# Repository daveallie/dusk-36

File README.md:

<h1 align="center">Dusk 36 Keyboard</h1>

Dusk 36 is a 36-key low-profile split ergo keyboard based off https://github.com/weteor/3W6 and 
https://github.com/davidphilipbarr/Sweep.

The Dusk 36 is designed around the nice!nano v2.0 microcontroller in order to be a true wireless keyboard (no cables
between halves or from the keyboard to the computer). This board's layout was generated with 
[my fork of Ergogen](https://github.com/daveallie/ergogen/tree/daveallie-improvements) (which includes a few small 
changes), and then routed by hand in KiCad.

### PCB Preview

| Left                   | Right                   |
|------------------------|-------------------------|
|  |  |

### BOM

**Hardware for PCB**
- 2 x [nice!nano v2.0](https://keebd.com/products/nice-nano?variant=41688983240856)
- 1 x [Kailh Low Profile Switches Hot-swappable PCB Socket Sip socket Hot Plug (50 pack)](https://www.aliexpress.com/item/1005003575767699.html)
- 2 x [40 Pin Machined IC Breakable Female Header Strip](https://keebd.com/products/40-pin-machined-ic-breakable-female-header-strip?variant=40383060410520)
- Pins (pick one)
  - 48 x [Single Post Terminal Connector Through Hole Gold 0.020" (0.51mm) Dia](https://www.digikey.com.au/en/products/detail/mill-max-manufacturing-corp/3320-0-00-15-00-00-03-0/4147392)
  - 2 x [Mill-Max Low Profile Controller Pins (Pack of 25)](https://keebd.com/products/mill-max-low-profile-controller-pins-pack-of-25?variant=41055232458904)
- 2 x [EG1215AA Switch](https://www.digikey.com.au/en/products/detail/e-switch/EG1215AA/9559277)
- 2 x [PTS636 SK43 LFS button](https://www.digikey.com.au/en/products/detail/c-k/PTS636-SK43-LFS/10071716)
- 2 x [Polymer Lithium Ion Battery (LiPo) 3.7V 120mAh](https://core-electronics.com.au/lipo-polymer-lithium-ion-battery-120mah.html)
- 36 x SOD-123 diode

**Switches and Keycaps**
- 4 x [Kailh low profile Switch 1350 Chocolate Keyboard Switch RGB SMD kailh Mechanical Keyboard white stem clicky hand feeling (10 pack)](https://www.aliexpress.com/item/32959996455.html)
- 3 x [MBK Low Profile Keycaps - 1u Black (10 pack)](https://keebd.com/products/mbk-low-profile-keycaps?variant=41506944909464)
- 1 x [MBK Low Profile Keycaps - 1u Homing White (2 pack)](https://keebd.com/products/mbk-low-profile-keycaps?variant=41506944811160)
- 1 x [MBK Low Profile Keycaps - 1.5u Black (5 pack)](https://keebd.com/products/mbk-low-profile-keycaps?variant=41506944975000)

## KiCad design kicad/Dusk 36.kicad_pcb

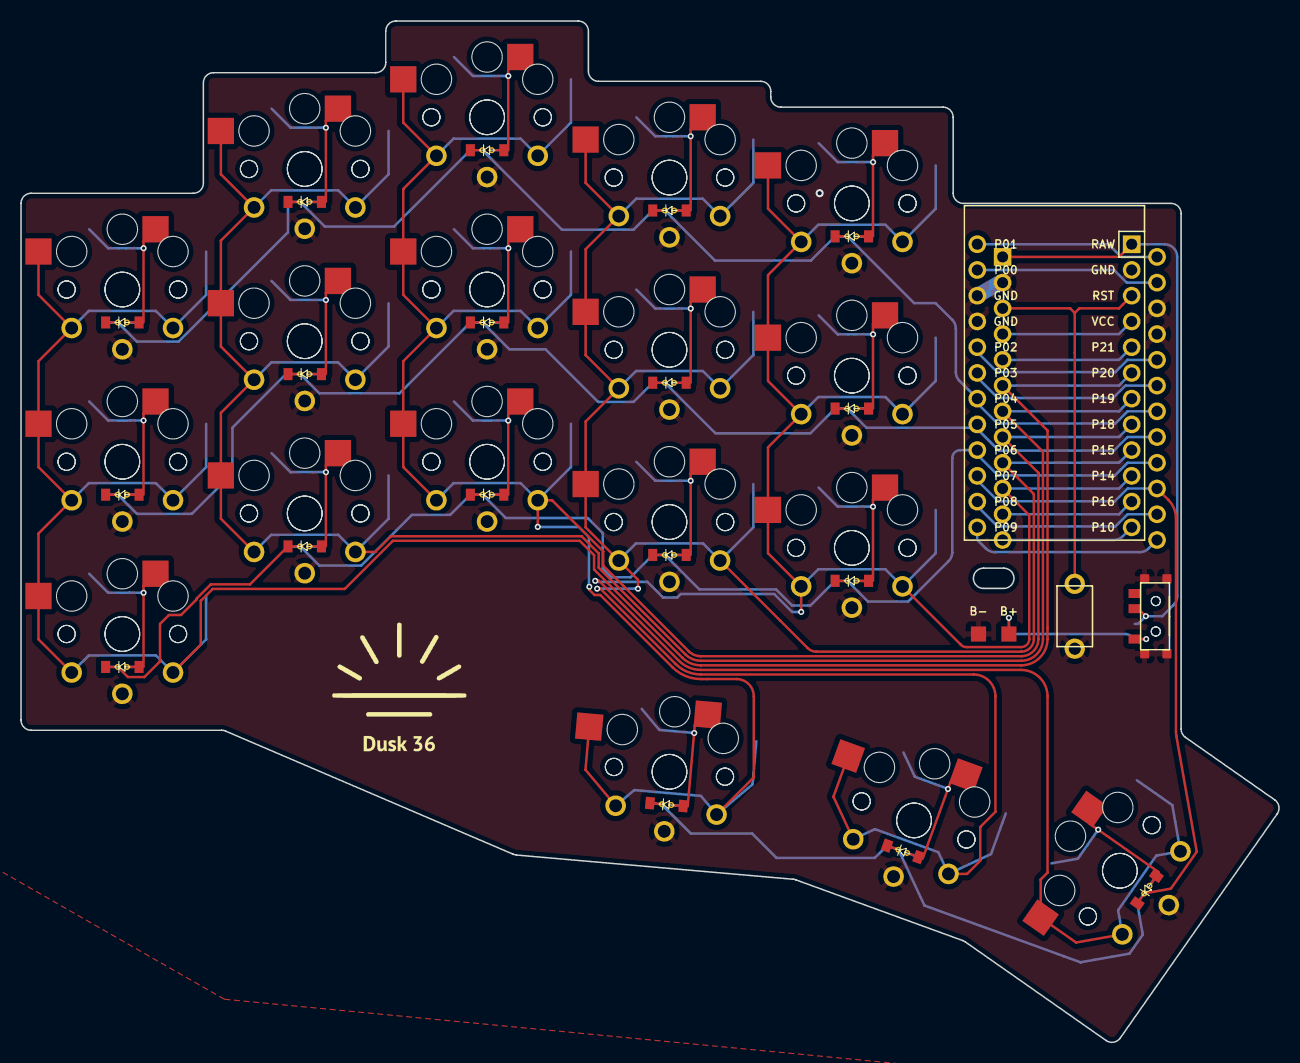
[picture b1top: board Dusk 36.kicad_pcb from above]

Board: 2 copper layers, 124.2 x 100.8 mm, 61 parts (1 on the bottom side), 41 nets.

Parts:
B1: SW_TACT_PTS636_SK43_LFS
D1, D2, D3, D4, D5, D6, D7, D8, D9, D10, D11, D12, D13, D14, D15, D16, D17, D18: ComboDiode
MCU1, MCU2: ProMicro
PAD1, PAD2: SMDPad
S1, S2, S3, S4, S5, S6, S7, S8, S9, S10, S11, S12, S13, S14, S15, S16, S17, S18, S19, S20, S21, S22, S23, S24, S25, S26, S27, S28, S29, S30, S31, S32, S33, S34, S35, S36: PG1350
T1, T2: SPDT_C128955

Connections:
BPos: PAD1.1, T1.1, T2.3
GND: B1.1, MCU1.2, MCU1.15, MCU1.16, MCU2.2, MCU2.15, MCU2.16, PAD2.1, S2.2, S4.2, S6.2, S8.2, S10.2, S12.2, S14.2, S16.2, S18.2, S20.2, S22.2, S24.2, S26.2, S28.2, S30.2, S32.2, S34.2, S36.2
P0: MCU1.14, MCU2.14
P1: MCU1.13, MCU2.13
P2: MCU1.17, MCU2.17
P3: MCU1.18, MCU2.18
P4: D3.1, D6.1, D9.1, D12.1, D15.1, MCU1.19, MCU2.19
P5: D2.1, D5.1, D8.1, D11.1, D14.1, MCU1.20, MCU2.20
P6: D1.1, D4.1, D7.1, D10.1, D13.1, MCU1.21, MCU2.21
P7: D16.1, D17.1, D18.1, MCU1.22, MCU2.22
P8: MCU1.23, MCU2.23
P9: MCU1.24, MCU2.24
P10: MCU1.12, MCU2.12
P14: MCU1.10, MCU2.10, S25.2, S26.1, S27.2, S28.1, S29.2, S30.1, S35.2, S36.1
P15: MCU1.9, MCU2.9, S19.2, S20.1, S21.2, S22.1, S23.2, S24.1, S33.2, S34.1
P16: MCU1.11, MCU2.11
P18: MCU1.8, MCU2.8, S13.2, S14.1, S15.2, S16.1, S17.2, S18.1, S31.2, S32.1
P19: MCU1.7, MCU2.7, S7.2, S8.1, S9.2, S10.1, S11.2, S12.1
P20: MCU1.6, MCU2.6, S1.2, S2.1, S3.2, S4.1, S5.2, S6.1
P21: MCU1.5, MCU2.5
RAW: MCU1.1, MCU2.1, T1.2, T2.2
RST: B1.2, MCU1.3, MCU2.3
VCC: MCU1.4, MCU2.4
far_thumb: D18.2, S35.1
home_thumb: D17.2, S33.1
index_bottom: D10.2, S19.1
index_home: D11.2, S21.1
index_top: D12.2, S23.1
inner_bottom: D13.2, S25.1
inner_home: D14.2, S27.1
inner_top: D15.2, S29.1
middle_bottom: D7.2, S13.1
middle_home: D8.2, S15.1
middle_top: D9.2, S17.1
near_thumb: D16.2, S31.1
pinky_bottom: D1.2, S1.1
pinky_home: D2.2, S3.1
pinky_top: D3.2, S5.1
ring_bottom: D4.2, S7.1
ring_home: D5.2, S9.1
ring_top: D6.2, S11.1

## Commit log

2022-08-23 Cleanup file
2022-08-23 Fix up PCB outline
2022-08-25 Cleanup ergogen
2022-08-28 Update ergogen file and route board
2022-08-31 Cleanup traces and make ✨curvy✨
2022-09-04 Add pcb art
2022-09-04 Rename board to Dusk 36
2022-09-04 Add gerber files
2022-09-04 Add README.md
2022-10-12 Update pins option in README BOM
2022-10-12 Add basic ZMK config
2022-10-14 Add Lower and Upper layers
2022-10-14 Add build.sh for local ZMK firmware building
2022-10-14 Cleanup keymap
2022-10-14 Add qwerty base to keymap and add readme to ZMK directory
2022-10-18 Fix keypad keycodes
2022-10-19 Add mosaic shortcuts to adjust layer
2022-10-19 Fix local build script
2022-10-20 Replace keypad numbers with number row numbers for better shortcut support
2022-10-21 Add auto-GUI to comma, period, and slash keys
2022-10-26 Add case f3d and stl files
2022-11-03 Add assembled photo
2024-07-19 Bump to latest zmk
2024-07-19 Update Github Actions libraries
2024-07-19 Fix artifact naming
2024-07-19 Update kicad files to latest version
